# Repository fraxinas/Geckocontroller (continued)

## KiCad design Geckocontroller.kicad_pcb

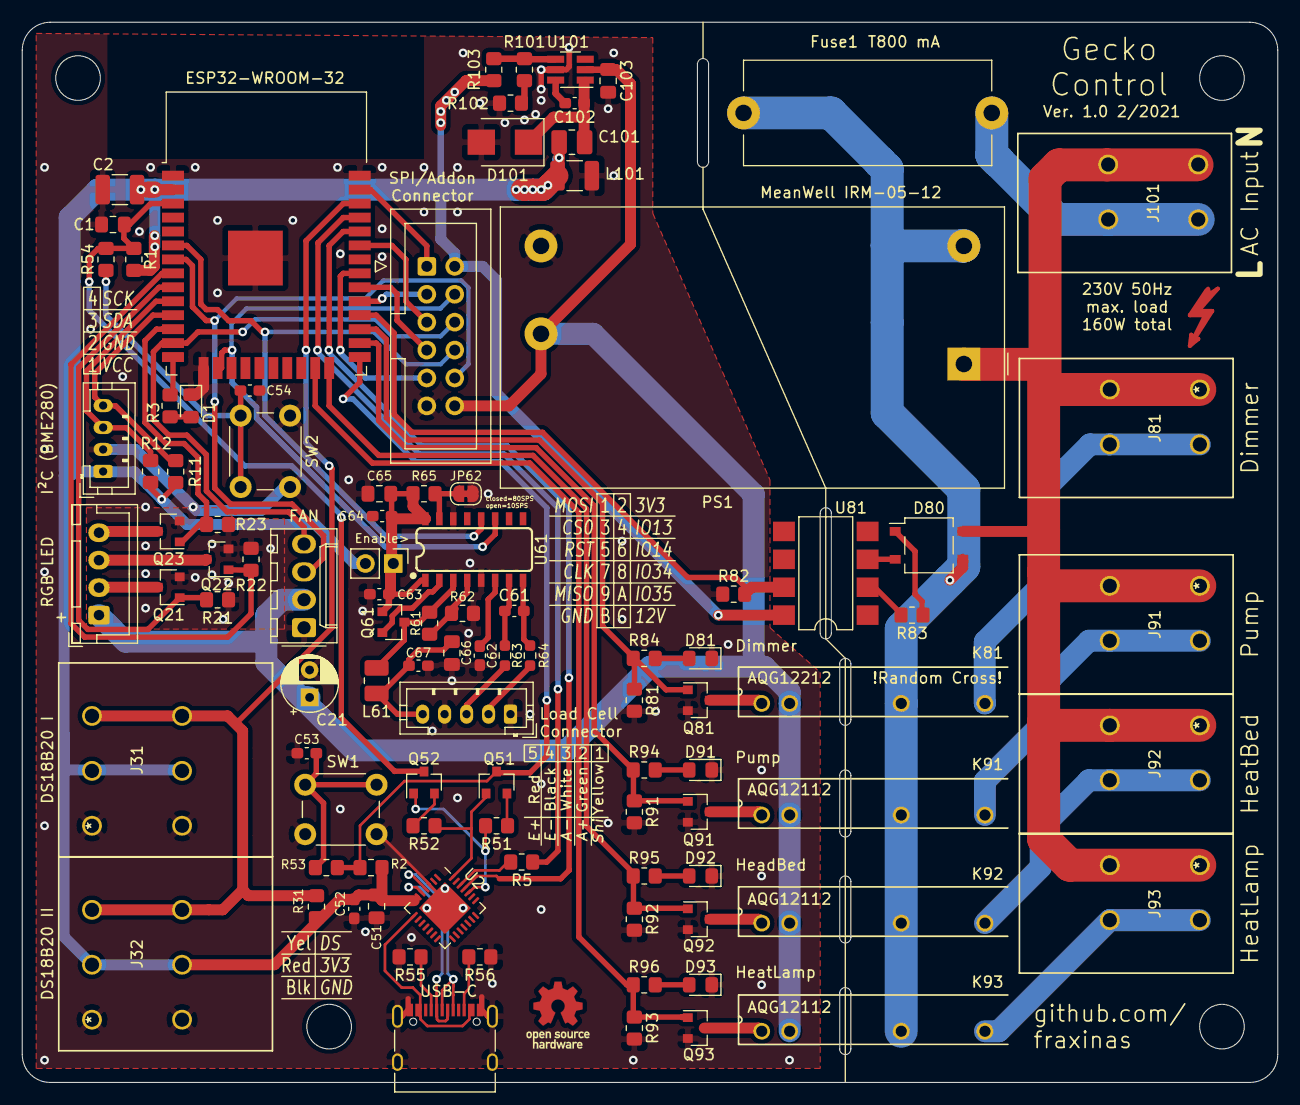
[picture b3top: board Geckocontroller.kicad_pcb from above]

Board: 2 copper layers, 114.3 x 96.5 mm, 98 parts (0 on the bottom side), 77 nets.

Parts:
C1, C51, C65, C66, C103: 10µF; C_0805_2012Metric_Pad1.18x1.45mm_HandSolder
C2, C101: 22µF; C_1210_3225Metric_Pad1.33x2.70mm_HandSolder
C21: 47µF 25V; CP_Radial_D5.0mm_P2.50mm
C52, C53, C54, C61, C62, C63, C64, C67: 100nF; C_0603_1608Metric_Pad1.08x0.95mm_HandSolder
C102: 22nF; C_0603_1608Metric_Pad1.08x0.95mm_HandSolder
D1, D81, D91, D92, D93: LED; LED_0805_2012Metric_Pad1.15x1.40mm_HandSolder
D80: D_Bridge_+-AA; TO-269AA
D101: B240; D_SMB
Fuse1: T800 mA; Fuseholder_Cylinder-5x20mm_Stelvio-Kontek_PTF78_Horizontal_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
J11: I²C (BME280); JST_PH_B4B-PH-K_1x04_P2.00mm_Vertical
J21: RGB LED; JST_XH_B4B-XH-A_1x04_P2.50mm_Vertical
J31: DS18B20 I; 2604-1103
J32: DS18B20 II; 2604-1103
J40: FAN; Molex_KK-254_AE-6410-04A_1x04_P2.54mm_Vertical
J51: USB-C; USB_C_Receptacle_XKB_U262-16XN-4BVC11
J60: Load Cell Connector; JST_PH_B5B-PH-K_1x05_P2.00mm_Vertical
J70: SPI / Addon Connector; IDC-Header_2x06_P2.54mm_Vertical
J81: Dimmer; 2604-1102
J91: Pump; 2604-1102
J92: HeatBed; 2604-1102
J93: HeatLamp; 2604-1102
J101: AC Input; 2604-1102
JP61: Enable>; PinHeader_1x02_P2.54mm_Vertical
JP62: Jumper; SolderJumper-2_P1.3mm_Bridged_RoundedPad1.0x1.5mm
K81: AQG12212; AQG22224
K91, K92, K93: AQG12112; AQG22224
L61: 3.3µH; L_1008_2520Metric_Pad1.43x2.20mm_HandSolder
L101: 4.7µH; L_1008_2520Metric_Pad1.43x2.20mm_HandSolder
PS1: MeanWell IRM-05-12; Converter_ACDC_MeanWell_IRM-05-xx_THT
Q21, Q22, Q23, Q81, Q91, Q92, Q93: AO3400A; SOT-23
Q51, Q52: S8050; SOT-23
Q61: S8550; SOT-23
R1, R2, R51, R52: 12k; R_0805_2012Metric_Pad1.20x1.40mm_HandSolder
R3, R5, R53, R54, R84, R94, R95, R96: 470R; R_0805_2012Metric_Pad1.20x1.40mm_HandSolder
R11, R12, R31: 4k7; R_0805_2012Metric_Pad1.20x1.40mm_HandSolder
R21, R22, R23, R81, R91, R92, R93: 68k; R_0805_2012Metric_Pad1.20x1.40mm_HandSolder
R55, R56: 5k1; R_0805_2012Metric_Pad1.20x1.40mm_HandSolder
R61, R103: 47k±1%; R_0805_2012Metric_Pad1.20x1.40mm_HandSolder
R62: 30k1±1%; R_0805_2012Metric_Pad1.20x1.40mm_HandSolder
R63, R64: 100R; R_0603_1608Metric_Pad0.98x0.95mm_HandSolder
R65, R82: 10k; R_0805_2012Metric_Pad1.20x1.40mm_HandSolder
R83: 330kR; R_0805_2012Metric_Pad1.20x1.40mm_HandSolder
R101: 15k±1%; R_0805_2012Metric_Pad1.20x1.40mm_HandSolder
R102: 287R±1%; R_0805_2012Metric_Pad1.20x1.40mm_HandSolder
SW1, SW2: SW_Push; SW_PUSH_6mm
U1: ESP32-WROOM-32
U2: CP2102; QFN-28-1EP_5x5mm_P0.5mm_EP3.35x3.35mm
U61: HX711; SO16
U81: 6N138; SMDIP-8_W7.62mm
U101: ACT4088; SOT-23-6_Handsoldering

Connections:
+3V3: C2.1, C51.1, C52.1, C101.1, J11.1, J31.3, J31.4, J32.3, J32.4, J70.2, JP61.2, L101.2, R1.2, R2.1, R11.1, R12.1, R31.1, R103.1, U1.2, U2.6, U2.7, U81.8
+12V: C21.1, C103.1, J21.1, J40.2, J70.12, K81.+, K91.+, K92.+, K93.+, PS1.4, U101.2
/A+: J60.2, R64.1
/A-: J60.3, R63.1
/AVDD: L61.2, Q61.3, R61.1, U61.3
/Blue_out: Q23.1, R23.2, U1.12
/Boot_switch: C53.1, R53.1, SW1.2
/D+: J51.A6, J51.B6, U2.4
/D-: J51.A7, J51.B7, U2.5
/DS_in: J31.5, J31.6, J32.5, J32.6, R31.2, U1.36
/DTR: Q51.1, R52.2, U2.28
/Dimmer_out: Q81.1, R81.1, R84.1, U1.27
/E+: C66.2, C67.2, J60.5, L61.1
/Green_out: Q21.1, R21.2, U1.9
/I2C_SCK: J11.4, R11.2, U1.11
/I2C_SDI: J11.3, R12.2, U1.10
/L: Fuse1.1, J101.3, J101.4
/L': D80.3, Fuse1.2, K81.O1, K91.O1, K92.O1, K93.O1, PS1.2
/L_Dimmer: J81.3, J81.4, K81.O2
/L_Relay1: J91.3, J91.4, K91.O2
/L_Relay2: J92.3, J92.4, K92.O2
/L_Relay3: J93.3, J93.4, K93.O2
/N: D80.4, J81.1, J81.2, J91.1, J91.2, J92.1, J92.2, J93.1, J93.2, J101.1, J101.2, PS1.1
/RTS: Q52.1, R51.2, U2.24
/Red_out: Q22.1, R22.2, U1.8
/Relay1_out: Q91.1, R91.1, R94.1, U1.26
/Relay2_out: Q92.1, R92.1, R95.1, U1.24
/Relay3_out: Q93.1, R93.1, R96.1, U1.23
/Reset_switch: C54.1, R54.1, SW2.2
/TXD': R5.2, U1.35
/VBUS: J51.A4, J51.A9, J51.B4, J51.B9, U2.8
/ZX_in: R82.2, U1.28, U81.7
EN: C1.1, Q52.3, R1.1, R54.2, U1.3
FAN_PWM: J40.4, J70.6, U1.13
FAN_SIG: J40.3, J70.10, U1.7
GND: C1.2, C2.2, C21.2, C51.2, C52.2, C53.2, C54.2, C62.2, C63.2, C64.2, C65.2, C66.1, C67.1, C101.2, C103.2, D1.1, D81.1, D91.1, D92.1, D93.1, D101.2, J11.2, J31.1, J31.2, J32.1, J32.2, J40.1, J51.A1, J51.A12, J51.B1, J51.B12, J51.S1, J60.1, J60.4, J70.11, JP62.2, PS1.3, Q21.2, Q22.2, Q23.2, Q81.2, Q91.2, Q92.2, Q93.2, R21.1, R22.1, R23.1, R55.1, R56.1, R62.2, R81.2, R82.1, R91.2, R92.2, R93.2, R102.1, SW1.1, SW2.1, U1.1, U1.15, U1.38, U1.39, U2.3, U2.29, U61.5, U61.14, U101.5
HX_CLK: J70.4, U1.16, U61.11
HX_DATA: J70.8, U1.6, U61.12
IO0: Q51.3, R2.2, R53.2, U1.25
unnamed: C61.1, R63.2, U61.7
unnamed: C61.2, R64.2, U61.8
unnamed: C62.1, U61.6
unnamed: C63.1, C64.1, C65.1, JP61.1, Q61.1, R65.1, U61.1, U61.16
unnamed: C102.1, D101.1, L101.1, U101.1
unnamed: C102.2, U101.6
unnamed: D1.2, R3.2
unnamed: D80.1, R83.1
unnamed: D80.2, U81.3
unnamed: D81.2, R84.2
unnamed: D91.2, R94.2
unnamed: D92.2, R95.2
unnamed: D93.2, R96.2
unnamed: J21.2, Q21.3
unnamed: J21.3, Q22.3
unnamed: J21.4, Q23.3
unnamed: J51.A5, R55.2
unnamed: J51.B5, R56.2
unnamed: JP62.1, R65.2, U61.15
unnamed: K81.-, Q81.3
unnamed: K91.-, Q91.3
unnamed: K92.-, Q92.3
unnamed: K93.-, Q93.3
unnamed: Q51.2, R51.1
unnamed: Q52.2, R52.1
unnamed: Q61.2, U61.2
unnamed: R3.1, U1.14
unnamed: R61.2, R62.1, U61.4
unnamed: R83.2, U81.2
unnamed: R101.1, R102.2
unnamed: R101.2, R103.2, U101.4
RXD: U1.34, U2.25
SPI_CLK: J70.7, U1.30
SPI_CS0: J70.3, U1.29
SPI_MISO: J70.9, U1.31
SPI_MOSI: J70.1, U1.37
SPI_RES: J70.5, U1.33
TXD: R5.1, U2.26

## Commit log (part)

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2021-02-06 PCB: Initial commit
2021-02-07 Schema: Switch CP2104->CP2102 USB Interface
2021-02-07 Schema: ADD SPI Header
2021-02-07 Schema: Use ACT4088 Buck instead
2021-02-08 Schema: Name Nets, shuffle GPIO connections around
2021-02-08 Schema: Add status LEDs for Outputs
2021-02-08 PCB: Re-arrange PSU parts
2021-02-09 PCB: Add HX711 load cell input + PWM fan connector
2021-02-09 PCB: Silkscreen Inscriptions
2021-02-10 Schema: Calculate feedback and volt.div. resistors for Buck and HX711
2021-02-10 Schema+PCB: Switch GPIOs, add HX711 enable jumper
    * GPIO34 can only be used as input,
    so switch HX_CLK and FAN_SIG.
2021-02-11 Schema+PCB: Fix a few ERC issues, add warning symbols + QR Code
    Mark unconnected Pins with X's, set WAGO pins to passive
2021-02-14 PCB: Add Repairfox and Purple Gecko silkscreen prints
    Schema: move graphical boxes around a bit
2021-02-14 hardware: Add README containing circuitry calculations
2021-02-21 software: Add esphome basic config
2021-03-04 library: Add "bare" versions of WAGO terminal footprints
    add stackable versions with smaller courtyard &
    change silkscreen outline so that name print fits
2021-03-07 library: Add CP2102 QFN28 footprint modified for hand soldering
2021-03-07 hardware: Update Schematic plot
2021-04-10 hardware: Add S8050 & S8550 symbols with fixed pinout
    Fixes auto programming and HX711 Load Cell AVDD
2021-04-11 hardware: Change footprint of optocoupler
    use a wider version, make it easier to solder
2021-04-11 software: Add HX711 & Fan PWM+Tacho, fix dimmer+BME parameters
2021-04-11 schema: Update schematic plot PDF
2021-04-12 Schema: Add Fan PWM integrator and MOSFET switch
2021-04-12 schema: Update schematic plot PDF (FAN switch)
2021-04-13 hardware: wire GPIO12 to addon header, layout improvements
    * add 6-pin UART header
    * new, larger OSHW logo
    * new, smaller solder jumper for HX711
    * switch RGB-LED & I2C modules and respective part numbers
    * renumber some USB programmer parts
    * improve silkscreen inscriptions
2021-04-14 PCB: Move around modules and masks a little more
    No functional changes
2021-04-15 Hardware: Update PCB renderings
2021-04-15 Readme: Add project diary
2021-04-16 Schema: Set data fields, use CP symbol for C11, renum R2, re-plot PDF
2021-04-20 Software: Add sunrise effect for scenic light
2021-04-22 Software: Add Lightning effect
2021-04-26 Software: Add template action for "Let it rain"
    * also add manual heat bed switch (defunct)
2021-04-27 Software: Fix lightning effect
2021-04-27 Software: Fix stopping of sunrise + sunset effects
2021-04-28 Software: Couple sunset + sunrise effects and daylight dimmer to astro sun
2021-04-29 Software/custom-components: add custom st7789v (WIP)
    * made optional pins optional
    * made dimensions configurable (240x240 crashes)
2021-04-29 Software: Bind Air and Heatbed Thermostats to weather forecast
2021-04-30 Software/custom-components: use DisplayBufferHeapList (WIP)
    * enables allocation of enough memory for a 240x240 TFT.
    * doesn't do anything yet, needs more work on array access operator
2021-05-03 Software: add status LED
2021-05-06 Console Schema: Start Geckoconsole schematic
2021-05-06 Console Schema: Use linear regulator, add buzzer & RGB
2021-05-07 Console Schema: Add footprints
2021-05-07 Console PCB: Start PCB, drop parts
2021-05-09 Console Hardware: Add Extension header, PCB silkscreen labels
2021-05-10 Console Software: add esphome yaml for Geckoconsole
2021-05-12 Console Software: Add more periphery
    * UART
    * MH-Z19
    * Rotary Encoder w/ button
    * Buzzer
    * Status LED
2021-05-14 Controller Software: Dallas properties
    * fix substrate sensor address
    * comment out absent heatbed sensor
    * increase interval (ease dimmer flicker)
2021-05-17 Readme: Update TODOs and project diary
2021-05-18 Controller Software: Remove unnecessary display code
    This will go into gecko-console
2021-05-23 Controller Software: Implement RainPumpOutput
    This is basically a `slow_pwm` variant, which does not force-off the output unless
    it was turned on before by a duty cycle. This means that the rain pump can be
    manually turned on and off aswell.
2021-05-25 Console Hardware (Library): Add VCNL4040 proxmity sensor symbol and footprint
2021-05-25 Console Schema: Add voltage-drop diode for WS2812 (for level shifting)
2021-05-27 Controller Software: Add manual Humidy control
2021-05-28 Software: Add README with calibration values for load cell
2021-05-31 Controller Schema: Add 2nd I2C Connector
2021-12-26 Software: Change/Add YAML keys in order to be compatible with esphome 2021.12.2
2022-01-06 Software: Rename Heat Bed -> Fogger, add humidity controller
2022-01-06 Software: Change nighttime color
2022-01-09 Software: Fast humidity sensor interval, add combined humidity (take greater value)
2022-01-09 Software: read and use rain and sky values from home assistant
2022-01-10 Software: implement daylight attenuation global
2022-01-12 Software: update README (add links)
2022-01-13 Software: Use threshold filter for I2C sensor clamping
2022-01-22 Hardware: Enumerate Jumper1 in Schema
2022-01-22 Software: Later Sunrise (+10°), brighter night colors
2022-01-25 Console Hardware: Convert Geckoconsole to KiCad 6
2022-01-27 Console PCB: Make ready for fab
    * rename layers according to Aisler Gerber specs
    * Silkscreen project lable
    * break-off-PCB drills
2022-01-29 Software: Tune humidity parameters
    * decrease hygro sensor update intervals
    * no min-power for fogger
    * PID values for humidity controller
2022-01-30 Software: Change momentary switches for rain & fog to buttons
2022-01-31 Software: Explicitely set LEDC PWM channels (fix blue tint)
2022-01-31 Software: Rework daylight controller
    * use different quantifiers for positive/negative attenuation
2022-01-31 Software: Add is_daytime global, switch between daylight and night heating lamps
2022-01-31 Software: Implement Thunderstorm & Lightning simulation
    * requires https://github.com/fraxinas/historic_weather/commit/2192a8d0
2022-02-01 Readme: Update TODOs, diary & HASS historic weather configuration docu
2022-02-02 Software: Refactor Thermostat daylight write_action
    * will now account for skycond and twilight
    * new linearizer regarding actual control value (>1.0) which
    applies weighted attenuation
    * increase transition duration to 30s
    Fixup: correct brightness on sky condition update
2022-02-04 Software: Improve Daylight write_action
    * simplify low-intensity attenuation
2022-02-05 Software: Implement Fan Thermo & Hygro classes for setting states through YAML
2022-02-05 gitignore: Move hardware ignores & adapt to Kicad 6
2022-02-08 Software: Recalibrate Scale
2022-02-11 custom_components: Try a skeleton custom python component (WIP, defunc)
2022-02-11 custom_components: Add configurables for MultiFan (WIP)
2022-02-11 custom_components: Implement multifan functionality (WIP)
2022-02-11 custom_components: Add fan traits to MultiFan
    * show speed slider in HASS
    * "Oscillating" switch turn off and on automatic speed processing
2022-02-11 Software: Use new MultiFan in geckocontroller
2022-02-21 Readme: Update Console TODOs + diary
2022-02-27 Software: add __pycache__ to gitignore
2022-02-27 custom_components: Add display_buffer with DisplayBufferHeapList
2022-02-27 Software Console: Add RTTTL buzzer playback service
2022-02-27 Software Console: CO2 Ampel with warning song
2022-02-27 Software Console: Menu Header bar, value display & setter
2022-02-27 custom_components: WIP on TerraLightNumber class
2022-02-27 Schema Console: Remove R55 (Fix Reset Button), graphical improvements
2022-02-28 Software Console: Fix rotary encoder jumpiness
    * by implementing a HASS updater timeout
    * also make encoder sensor internal
2022-03-01 custom_components: Big ST7789v need moar bits for pixel addresses
2022-03-01 custom_components: Highlight the active sector of Gauge and add additional width
2022-03-01 custom_components: Add set_mode argument to DisplayBuffer:gauge
2022-03-02 custom_components: Fix DisplayBuffer:gauge sector color for 50.0% case
2022-03-02 Software Console: Reorder menu, add fogger & rain buttons
2022-03-03 Software Console: Color update
    * use new color definition
    * use global colors for overview background rectangles
    * derive these from the diff between set and actual values
    * update on HASS sensor updates and simplify display paint function
2022-03-04 Software Console: Fix jumping climate controls (ignore HASS updates properly)
    * also account for possible rounding errors in rotary value range calculation
2022-03-04 Software Console: Splash screen + Menu indicator layout
2022-03-04 custom_components: Add DisplayBuffer:color_picker method
2022-03-04 Software Console: Add Colorpicker to Gecko Console
2022-03-05 Software Console: Implement hue, saturation and brightness control
2022-03-06 Software Console: Use #defines for Constants & enum for subpage names
2022-03-06 Hardware Console: Start with HW Revision 2
    * include 2nd navigation button
    * move USB-C interface onto separate daughter board
    * hide VCNL4040 parts from PCB
    * turn ESP32 180°
    * move LCD pin header to top of board
    * switch a few GPIOs
2022-03-07 Hardware Console: Route PCB, Pannelize
2022-03-07 Readme: Update Console features & PCB renderings
2022-03-08 Hardware Library: Add Alps EC11J15 SMD Rotary Encoder footprint
2022-03-08 Hardware Console: Route USB daughter board & some more GPIO shuffling
2022-03-11 Readme: Update Console PCB renderings
2022-03-13 Software Console: Fix Overview diff (call correct script on weather values)
2022-03-14 Software Console: Fix weather/setpoint update actions
    * don't set inhibitor variable on HASS updates, only on rotary action
2022-03-14 Software Console: Improve RTTTL playback
    * use on_prepare_playback automation callback to increase the display
    update interval to 15s during RTTTL playback for correct timing
    * use on_playback_finished to set the display update interval back to 500ms
2022-03-15 Console Software: use new PollingComponent::reschedule_update method
    requires https://github.com/esphome/esphome/pull/3294
2022-03-17 Software Console: update LCD only if contents change, not continously
2022-03-25 Software Console: Switch PINs to Hardware Revision 2.0
2022-04-05 Software console: Add common header
2022-04-05 Hardware Library: Add Footprint for Buzzer FUET 9650B
    * polarity marking
    * larger pads for improved hand-solderability
2022-11-09 Software Console: Switch RGB LED driver class to neopixelbus
2022-11-09 Software Console: Add RF Transmitter for ceiling fan
2026-06-15 Software Controller: Port to ESPHome 2026.5 + reorganize external components
    Port gecko.yaml (geckocontroller) from the removed-API state of ESPHome
    2023.7.0 to 2026.5.x:
    - esphome: platform/board -> dedicated esp32: block (arduino framework)
    - ota: add required platform: esphome
    - dallas: -> one_wire: (gpio) + dallas_temp sensors
    - bme280 -> bme280_i2c (component split)
2026-06-15 Software Controller: Source vicinity temperature from a Home Assistant entity
    Vicinity (the room temperature where the terrarium stands) now comes from Home
    Assistant instead of the onboard probe: temperature_vicinity is a homeassistant
    sensor subscribed to sensor.terrarium_vicinity_temperature. In HA, point a
    Template/helper sensor with that entity_id at whichever room sensor you want —
    the source can be changed there without reflashing.
    ESPHome subscribes to a fixed entity_id at compile time, so the entity choice is
2026-06-15 Software Controller: Take vicinity from climate.arbeit current_temperature
    The vicinity room temperature is the current temperature (Ist-Temperatur) of the
    climate.arbeit entity. Read it directly via the homeassistant sensor's attribute
    option (entity_id: climate.arbeit, attribute: current_temperature) instead of a
    separate template helper, so no HA-side helper is needed.
